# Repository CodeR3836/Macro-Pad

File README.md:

<h1 align="center">
  MacroPad
</h1>

<h4 align="center">
  A custom, open-source mechanical macro-pad .
</h4>

<div align="center">

</div>

<br>

##  Key Features

* **Brain:** Powered by the compact and capable **Arduino Pro Micro**.
* **Firmware:** Runs on **QMC Firmware**  for incredibly easy keymap customization without needing to recompile.
* **Display:** Integrated **0.96" OLED (128×64)** for real-time layer feedback, stats, or custom graphics.
* **Matrix:** A clean **4×3 Key Matrix** layout complete with diode orientation for robust anti-ghosting.
* **Encoder** A rotary encoder with push button for changing volumn.
* **Function** With fn feature it has total 12+12 = 24 working Keys

---

## Hardware Design

This project was built entirely from scratch, bridging custom PCB design with 3D modeling. 

##  Credits & Acknowledgments

This project wouldn't be possible without these incredible open-source tools and communities:

* **[KiCad](https://www.kicad.org/)** for the phenomenal open-source PCB design suite.
* **[Autodesk Fusion 360](https://www.autodesk.com/products/fusion-360/)** for the case design environment.

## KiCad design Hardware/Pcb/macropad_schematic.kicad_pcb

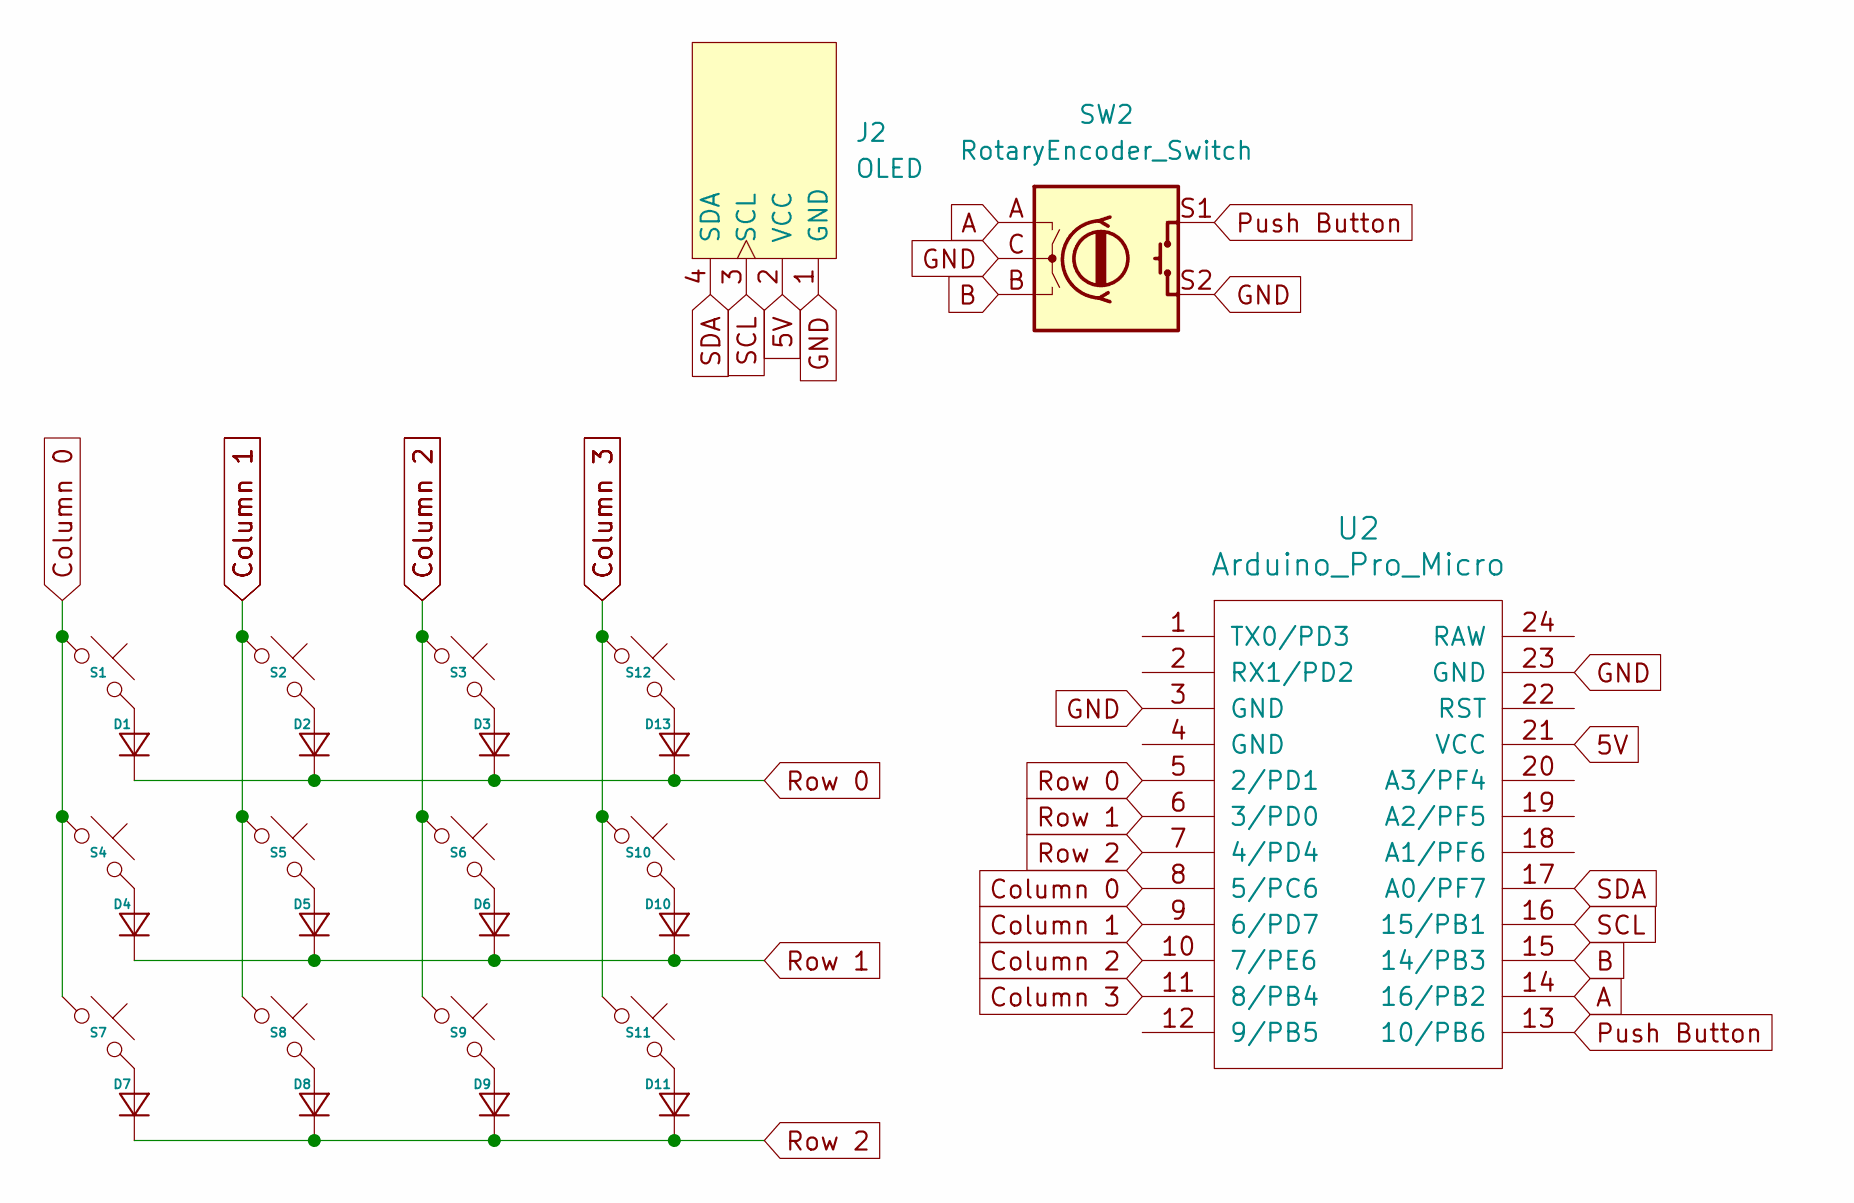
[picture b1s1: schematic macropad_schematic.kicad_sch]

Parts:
D1, D2, D3, D4, D5, D6, D7, D8, D9, D10, D11, D13: Diode_DO-35
J2: OLED; OLED_128x32
S1, S2, S3, S4, S5, S6, S7, S8, S9, S10, S11, S12: MX_PCB_1.00u
SW2: RotaryEncoder_Switch; Encoder_EC11_MX
U2: Arduino_Pro_Micro

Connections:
5V: J2.2 (VCC), U2.21 (VCC)
A: SW2.A, U2.14 (16/PB2)
B: SW2.B, U2.15 (14/PB3)
Column 0: S1.1, S4.1, S7.1, U2.8 (5/PC6)
Column 1: S2.1, S5.1, S8.1, U2.9 (6/PD7)
Column 2: S3.1, S6.1, S9.1, U2.10 (7/PE6)
Column 3: S10.1, S11.1, S12.1, U2.11 (8/PB4)
GND: J2.1 (GND), SW2.C, SW2.S2, U2.3 (GND), U2.23 (GND)
unnamed: D1.2 (A), S1.2
unnamed: D2.2 (A), S2.2
unnamed: D3.2 (A), S3.2
unnamed: D4.2 (A), S4.2
unnamed: D5.2 (A), S5.2
unnamed: D6.2 (A), S6.2
unnamed: D7.2 (A), S7.2
unnamed: D8.2 (A), S8.2
unnamed: D9.2 (A), S9.2
unnamed: D10.2 (A), S10.2
unnamed: D11.2 (A), S11.2
unnamed: D13.2 (A), S12.2
Push Button: SW2.S1, U2.13 (10/PB6)
Row 0: D1.1 (K), D2.1 (K), D3.1 (K), D13.1 (K), U2.5 (2/PD1)
Row 1: D4.1 (K), D5.1 (K), D6.1 (K), D10.1 (K), U2.6 (3/PD0)
Row 2: D7.1 (K), D8.1 (K), D9.1 (K), D11.1 (K), U2.7 (4/PD4)
SCL: J2.3 (SCL), U2.16 (15/PB1)
SDA: J2.4 (SDA), U2.17 (A0/PF7)

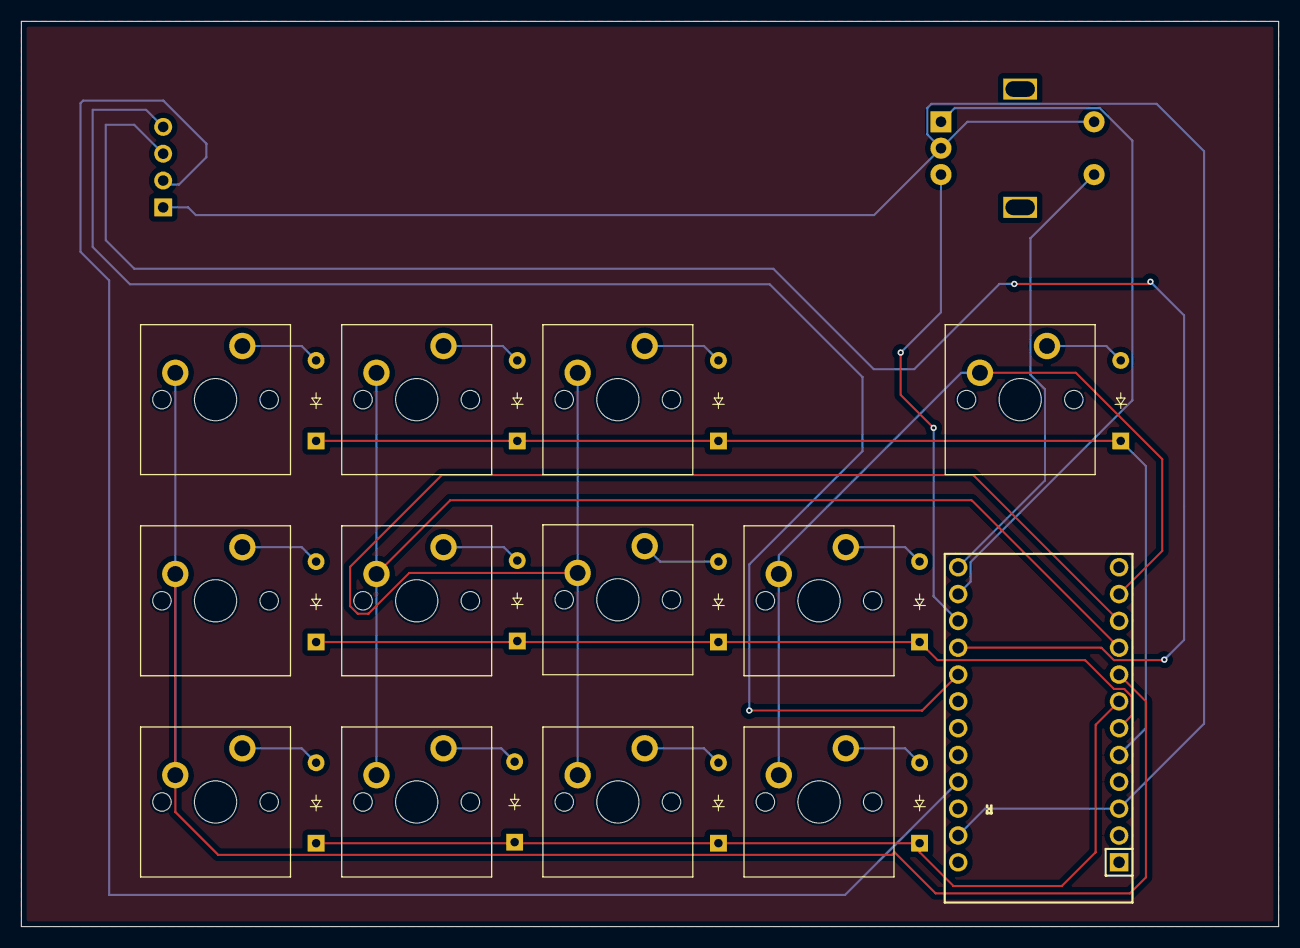
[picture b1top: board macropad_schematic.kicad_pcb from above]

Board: 2 copper layers, 119.1 x 85.7 mm, 27 parts (0 on the bottom side), 26 nets.
